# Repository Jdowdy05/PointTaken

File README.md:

# Point Taken — An Optical Tactile Fingertip

A compact optical tactile fingertip built around the **ams OSRAM TMF8829**. A soft silicone surface deforms under contact; the sensor observes the changing distance to its reflective inner layer. Force and contact information must be obtained through calibration.

*Connected electronics and exploded sensor assembly. Cable routing and exploded spacing are schematic.*

*Expected sensing principle. The zone projection and deformation example are illustrative, not calibrated measurements.*

## Repository layout

| Folder | Contents |
| --- | --- |
| [PCBs/](PCBs/) | Native KiCad projects for the five-sensor controller, single-sensor validation rig and fingertip board, plus shared symbols, footprints and 3D reference models. |
| [CAD/Sensor/](CAD/Sensor/) | Corrected sensor housing, one-piece cap retainer, optical parts, compliant-surface geometry, assembled STEP and printable rigid-part STLs. |
| [docs/](docs/) | Material notes, assembly instructions, harness pinout and manufacturer references. |

## Design specifications

| Property | Current design |
| --- | --- |
| Sensing IC | TMF8829 direct time-of-flight sensor; up to **48 ×32 zones** and **940 nm** near-infrared illumination. |
| Sensor enclosure | **24.2 mm wide ×44.5 mm high ×33.8 mm deep**, including the rear locating posts. |
| Fingertip PCB | **10 ×15 mm**, four copper layers, one TMF8829 and four 1.20 mm mounting holes. |
| Main controller | **50 ×50 mm**, six layers, STM32H573ZIT6 and up to five sensor ports; placement complete, **unrouted**. |
| Validation controller | **50 ×40 mm**, six layers, STM32H562RIT6 and one sensor port; routed prototype. |
| Sensor connection | 16-conductor JST NSHD wire harness; SPI primary, optional I3C/I2C lines. |
| Supply architecture | Protected 5 V USB-C controller input; 3.3 V and 1.8 V sensor rails, with an explicit I/O supply. |
| Compliant skin | Nominal **0.90 mm black outer layer +0.30 mm white inner layer**, 1.20 mm total. |
| Target-motion allowance | **6 mm** optical travel allocation; not a measured deformation or force rating. |
| Front retention | **One-piece ring**, three M2 ×6 screws, mechanically captured silicone flange/bead. |
| Rear retention | Two **M2 ×8 screws** for the standalone sensor; side-loaded M2 nuts bear on 4 mm housing shoulders. |

IC capabilities are from the [TMF8829 manufacturer information](https://ams-osram.com/products/sensor-solutions/direct-time-of-flight-sensors-dtof/ams-tmf8829-48x32-multi-zone-time-of-flight-sensor). They do not establish this prototype's effective tactile resolution, frame rate or calibrated force accuracy.

## What the deformable surface should be made from

The current prototype material candidate is **Smooth-On Ecoflex 00-30 platinum-cure silicone**, cast as a bonded two-layer membrane:

- **Outside:** approximately 0.90 mm of black-pigmented silicone to provide the contact surface and block ambient light.
- **Inside:** approximately 0.30 mm of white, titanium-dioxide-filled silicone to provide a diffuse reflective target at 940 nm.

The flexible cap is a cast silicone part. The files in `CAD/Sensor/print/` are the rigid parts intended for 3D printing; compliant-surface meshes describe the casting geometry.

[Ecoflex 00-30 manufacturer instructions](https://www.smooth-on.com/products/ecoflex-00-30/) specify a 1A:1B base mix. Follow the current technical bulletin for preparation and curing. **Pigment/TiO₂ loading and the two-layer bonding process are not yet qualified** for this cap. Black appearance alone does not prove infrared opacity, and white appearance does not establish adequate sensor return. See [Materials](docs/Materials.md) before casting.

## Sensitivity and load targets

These are **design targets, not measured specifications**:

- Detect **0.5 N normal contact**, at least five standard deviations above unloaded repeatability noise over the central 80% of the contact surface.
- Stretch goal: **0.10–0.25 N** detection.
- Produce at least **0.25 mm local target displacement at 0.5–1.0 N** centre load.
- Original mechanical goals: **30 N normal load and 75 N brief overload**. These have not been established for the current cap/housing.

The current state is **a CAD-checked hardware prototype awaiting physical qualification**. CAD clearance checks do not prove sensitivity, tear resistance, layer adhesion, fatigue, creep or overload survival. The single-sensor validation rig and fingertip PCB have routing; the five-sensor controller remains on manufacturing hold. No fabrication or assembly approval is implied by this publication.

## Open and build

1. Open a `.kicad_pro` from [PCBs/](PCBs/) using **KiCad 10** with its standard libraries installed. Project-local library paths are portable.
2. Open [sensor_assembly.step](CAD/Sensor/sensor_assembly.step) in FreeCAD or another STEP-compatible CAD tool. All CAD dimensions are millimetres.
3. Use the **five rigid-part STLs** in [CAD/Sensor/print/](CAD/Sensor/print/), and read the [assembly instructions](docs/Assembly.md). The corrected main housing and one-piece retainer are included.
4. Verify printed nut fits, layer construction and the actual electronics before powered testing. Calibrate the finished silicone article before interpreting deformation as force.

The STEP files provide editable solid geometry; native parametric feature history is not included in this publication. Manufacturer reference documents and component models are identified in [References](docs/References.md).

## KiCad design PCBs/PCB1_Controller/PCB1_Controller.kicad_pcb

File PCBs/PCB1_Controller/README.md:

# PCB1 Controller

Open [PCB1_Controller.kicad_pro](PCB1_Controller.kicad_pro) in KiCad 10.

Five-sensor controller; placement only, zero tracks/vias. Manufacturing hold.

- [Top copper/silkscreen preview](previews/top.svg)
- [Bottom copper/silkscreen preview](previews/bottom.svg)
- [Schematic pages](previews/schematics/)

Keep the shared connector and 3D-model folders alongside the board project. See the [PCB index](../README.md) for library setup and status.

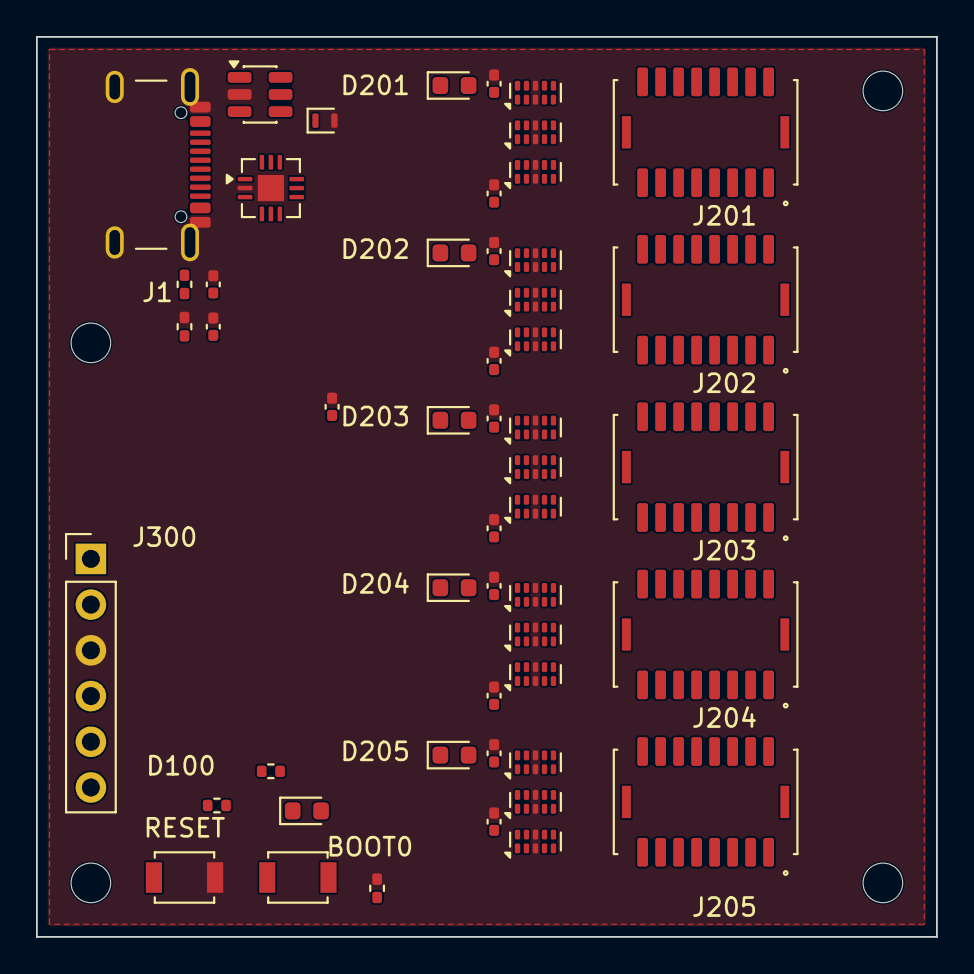
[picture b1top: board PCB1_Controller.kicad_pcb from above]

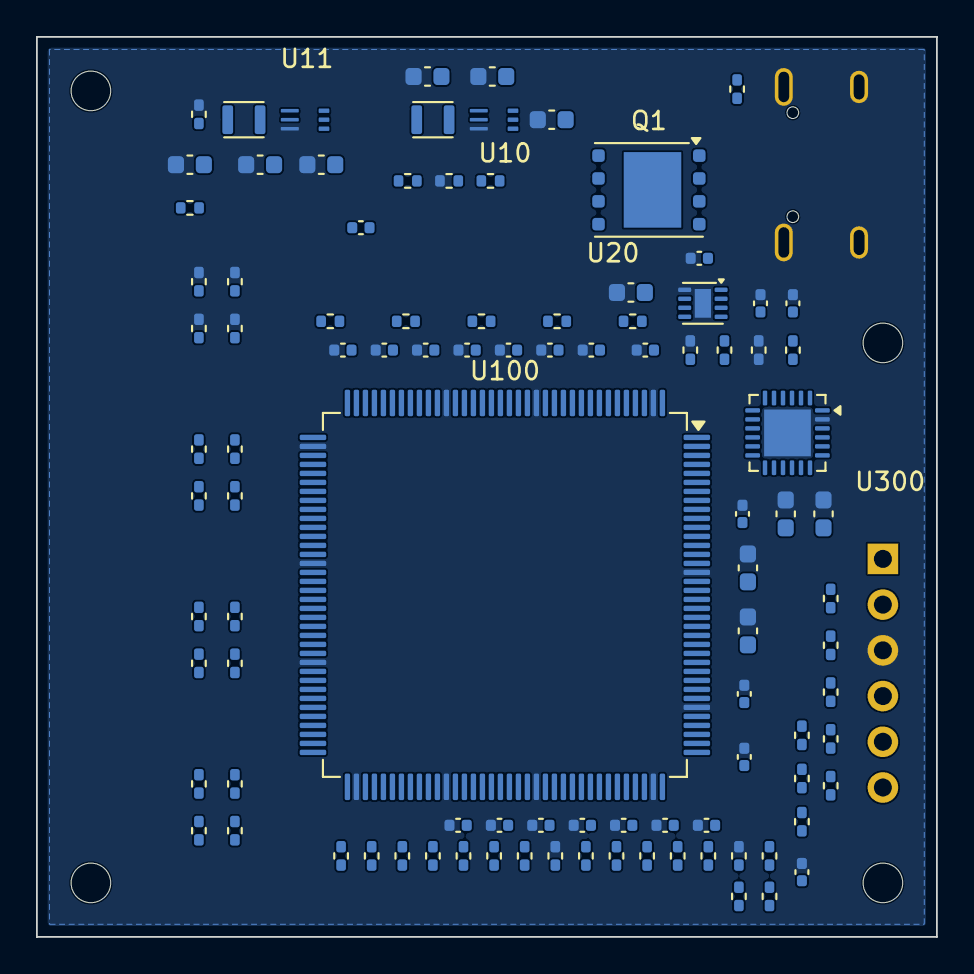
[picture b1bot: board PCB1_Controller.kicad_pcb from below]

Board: 6 copper layers, 50.0 x 50.0 mm, 153 parts (98 on the bottom side), 103 nets, no tracks yet.

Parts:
C1, C2: 330pF; C_0402_1005Metric
C3: 100nF 50V; C_0402_1005Metric
C4: 2.2uF 50V; C_0603_1608Metric
C5, C201, C202, C203, C204, C205, C211, C212, C213, C214, C215, C260, C303: 1uF; C_0402_1005Metric
C6: 3.3nF 50V; C_0402_1005Metric
C10, C20, C330, C340: 4.7uF; C_0603_1608Metric
C11, C12, C21, C22: 10uF; C_0603_1608Metric
C13: 120pF; C_0402_1005Metric
C300, C304, C310, C311, C312, C313, C314, C315, C316, C317, C318, C319, C320, C321, C322, C323, C341, C342: 100nF; C_0402_1005Metric
C301, C302: 2.2uF; C_0603_1608Metric
D1: ESDA25P35-1U1M; ST_QFN-2L_1.6x1.0mm
D100: MCU_STATUS green; LED_0603_1608Metric
D201: TOF1_DATA green; LED_0603_1608Metric
D202: TOF2_DATA green; LED_0603_1608Metric
D203: TOF3_DATA green; LED_0603_1608Metric
D204: TOF4_DATA green; LED_0603_1608Metric
D205: TOF5_DATA green; LED_0603_1608Metric
J1: USB4105-GF-A-120; USB_C_Receptacle_GCT_USB4105-xx-A_16P_TopMnt_Horizontal
J201, J202, J203, J204, J205: BM16B-NSHDZS-TFT; JST_BM16B-NSHDZS-TFT_2x08_P1.00mm_Vertical
J300: TSW-106-07-G-S SWD; PinHeader_1x06_P2.54mm_Vertical
L10, L11: 0.47uH; TDK_TFM201610ALM-R47MTAA_2.0x1.6mm
MH1, MH2, MH3, MH4: M2 2.2mm NPTH; MountingHole_2.2mm_M2
Q1: CSD17577Q5A; TI_CSD17577Q5A_DQJ_VSONP-8_4.9x6.0mm
R1: 80.6k; R_0402_1005Metric
R2: 24k; R_0402_1005Metric
R3, R5, R211, R212, R213, R214, R215, R300, R301: 10k; R_0402_1005Metric
R4, R262, R302, R303, R309: 0R; R_0402_1005Metric
R6: 681R; R_0402_1005Metric
R10: 450k; R_0402_1005Metric
R11, R12, R20, R201, R202, R203, R204, R205, R221, R222, R223, R224, R225, R231, R232, R233, R234, R235, R311, R312: 100k; R_0402_1005Metric
R241, R242, R243, R244, R245, R246, R247, R248, R249, R250: 22R; R_0402_1005Metric
R260, R261: 2.2k; R_0402_1005Metric
R271, R272, R273, R274, R275, R310: 1k; R_0402_1005Metric
R304, R305: 0R DNP; R_0402_1005Metric
R306: 22.1k DNP; R_0402_1005Metric
R307: 47.5k DNP; R_0402_1005Metric
R308: 1k DNP; R_0402_1005Metric
SW100: RESET B3U-1000P; SW_SPST_B3U-1000P
SW101: BOOT0 B3U-1000P; SW_SPST_B3U-1000P
U1: TCPP01-M12; QFN-12-1EP_3x3mm_P0.5mm_EP1.45x1.45mm
U2: USBLC6-2SC6; SOT-23-6
U10: TPS62826DMQ 3.3V; TI_DMQ0006A_VSON-HR-6_1.5x1.5mm
U11: TPS6282618DMQ 1.8V; TI_DMQ0006A_VSON-HR-6_1.5x1.5mm
U20: TPS259531DSGR; DFN-8-1EP_2x2mm_P0.5mm_EP0.9x1.6mm
U100: STM32H573ZIT6; LQFP-144_20x20mm_P0.5mm
U300: CP2102N-A02-GQFN24 DNP; QFN-24-1EP_4x4mm_P0.5mm_EP2.6x2.6mm
U401: ESD204DQA TOF1 SPI; USON-10_2.5x1.0mm_P0.5mm
U402: ESD204DQA TOF1 AUX; USON-10_2.5x1.0mm_P0.5mm
U403: ESD204DQA TOF1 DET; USON-10_2.5x1.0mm_P0.5mm
U404: ESD204DQA TOF2 SPI; USON-10_2.5x1.0mm_P0.5mm
U405: ESD204DQA TOF2 AUX; USON-10_2.5x1.0mm_P0.5mm
U406: ESD204DQA TOF2 DET; USON-10_2.5x1.0mm_P0.5mm
U407: ESD204DQA TOF3 SPI; USON-10_2.5x1.0mm_P0.5mm
U408: ESD204DQA TOF3 AUX; USON-10_2.5x1.0mm_P0.5mm
U409: ESD204DQA TOF3 DET; USON-10_2.5x1.0mm_P0.5mm
U410: ESD204DQA TOF4 SPI; USON-10_2.5x1.0mm_P0.5mm
U411: ESD204DQA TOF4 AUX; USON-10_2.5x1.0mm_P0.5mm
U412: ESD204DQA TOF4 DET; USON-10_2.5x1.0mm_P0.5mm
U413: ESD204DQA TOF5 SPI; USON-10_2.5x1.0mm_P0.5mm
U414: ESD204DQA TOF5 AUX; USON-10_2.5x1.0mm_P0.5mm
U415: ESD204DQA TOF5 DET; USON-10_2.5x1.0mm_P0.5mm

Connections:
BOOT0: R301.1, SW101.1, U100.138
CC1_CONN: C1.1, J1.A5, U1.7
CC2_CONN: C2.1, J1.B5, U1.9
CP2102_DM: R305.2, U300.4
CP2102_DP: R304.2, U300.3
CP2102_RST_N: R308.2, U300.9
CP2102_VBUS_SENSE: R306.2, R307.1, U300.8
EFUSE_DVDT: C6.1, U20.1
EFUSE_FLT_N: R5.2, U20.6, U100.125
EFUSE_ILM: R6.1, U20.7
FB_3V3: C13.2, R10.2, R11.1, U10.3
GND: C1.2, C2.2, C3.2, C4.2, C5.2, C6.2, C10.2, C11.2, C12.2, C20.2, C21.2, C22.2, C201.2, C202.2, C203.2, C204.2, C205.2, C211.2, C212.2, C213.2, C214.2, C215.2, C260.2, C300.2, C301.2, C302.2, C303.2, C304.2, C310.2, C311.2, C312.2, C313.2, C314.2, C315.2, C316.2, C317.2, C318.2, C319.2, C320.2, C321.2, C322.2, C323.2, C330.2, C340.2, C341.2, C342.2, D1.2, J1.A1, J1.A12, J1.B1, J1.B12, J1.SH, J300.3, R2.2, R4.1, R4.2, R6.2, R11.2, R201.2, R202.2, R203.2, R204.2, R205.2, R301.2, R307.2, R312.2, SW100.2, U1.2, U1.13, U2.2, U10.4, U11.4, U20.8, U20.9, U100.16, U100.31, U100.38, U100.51, U100.61, U100.71, U100.83, U100.94, U100.107, U100.120, U100.130, U100.143, U300.2, U300.25, U401.3, U401.8, U402.3, U402.8, U403.3, U403.8, U404.3, U404.8, U405.3, U405.8, U406.3, U406.8, U407.3, U407.8, U408.3, U408.8, U409.3, U409.8, U410.3, U410.8, U411.3, U411.8, U412.3, U412.8, U413.3, U413.8, U414.3, U414.8, U415.3, U415.8
I3C1_SCL_SHARED: R260.2, U100.136, U402.1, U405.1, U408.1, U411.1, U414.1
I3C1_SDA_SHARED: R261.2, U100.137, U402.2, U405.2, U408.2, U411.2, U414.2
MCU_STATUS_LED_A: D100.2, R310.2
MCU_STATUS_LED_N: D100.1, U100.124
MCU_UART_RX: U100.78, U300.21
MCU_UART_TX: U100.77, U300.20
NRST_N: C300.1, J300.5, R300.2, SW100.1, U100.25
P1V8_TOF: C21.1, C22.1, C211.1, C212.1, C213.1, C214.1, C215.1, L11.2, U11.3
P3V3: C11.1, C12.1, C13.1, C201.1, C202.1, C203.1, C204.1, C205.1, C310.1, C311.1, C312.1, C313.1, C314.1, C315.1, C316.1, C317.1, C318.1, C319.1, C320.1, C321.1, C322.1, C323.1, C330.1, C340.1, C341.1, J300.1, L10.2, R3.1, R5.1, R10.1, R12.1, R20.1, R262.1, R271.1, R272.1, R273.1, R274.1, R275.1, R300.1, R308.1, R309.1, R310.1, SW101.2, U1.12, U100.6, U100.17, U100.30, U100.39, U100.52, U100.62, U100.72, U100.84, U100.95, U100.106, U100.108, U100.121, U100.131, U100.144, U300.5, U300.6, U300.7
PGOOD_1V8: R20.2, U11.2
PGOOD_3V3: R12.2, U10.2
SPI1_MISO: U100.42, U401.4
SPI1_MOSI: R242.2, U401.2
SPI1_MOSI_MCU: R242.1, U100.43
SPI1_SCK: R241.2, U401.1
SPI1_SCK_MCU: R241.1, U100.41
SPI2_MISO: U100.28, U404.4
SPI2_MOSI: R244.2, U404.2
SPI2_MOSI_MCU: R244.1, U100.29
SPI2_SCK: R243.2, U404.1
SPI2_SCK_MCU: R243.1, U100.69
SPI3_MISO: U100.112, U407.4
SPI3_MOSI: R246.2, U407.2
SPI3_MOSI_MCU: R246.1, U100.113
SPI3_SCK: R245.2, U407.1
SPI3_SCK_MCU: R245.1, U100.111
SPI4_MISO: U100.66, U410.4
SPI4_MOSI: R248.2, U410.2
SPI4_MOSI_MCU: R248.1, U100.67
SPI4_SCK: R247.2, U410.1
SPI4_SCK_MCU: R247.1, U100.65
SPI5_MISO: U100.20, U413.4
SPI5_MOSI: R250.2, U413.2
SPI5_MOSI_MCU: R250.1, U100.21
SPI5_SCK: R249.2, U413.1
SPI5_SCK_MCU: R249.1, U100.19
STM_USB_DM: R303.2, U100.103
STM_USB_DP: R302.2, U100.104
SWCLK: J300.4, U100.109
SWDIO: J300.2, U100.105
SWO: J300.6, U100.133
SW_1V8: L11.1, U11.5
SW_3V3: L10.1, U10.5
TCPP_DB_N: U1.10, U100.101
TCPP_FLT_N: R3.2, U1.11, U100.98
TOF1_CS_N: R231.2, U100.40, U401.5
TOF1_DET: R221.2, U100.26, U403.1
TOF1_EN: R201.1, U100.79, U402.4
TOF1_INT: R211.2, U100.80, U402.5
TOF1_LED_A: D201.2, R271.2
TOF1_LED_N: D201.1, U100.89
TOF2_CS_N: R232.2, U100.37, U404.5
TOF2_DET: R222.2, U100.27, U406.1
TOF2_EN: R202.1, U100.81, U405.4
TOF2_INT: R212.2, U100.82, U405.5
TOF2_LED_A: D202.2, R272.2
TOF2_LED_N: D202.1, U100.90
TOF3_CS_N: R233.2, U100.116, U407.5
TOF3_DET: R223.2, U100.44, U409.1
TOF3_EN: R203.1, U100.58, U408.4
TOF3_INT: R213.2, U100.59, U408.5
TOF3_LED_A: D203.2, R273.2
TOF3_LED_N: D203.1, U100.91
TOF4_CS_N: R234.2, U100.64, U410.5
TOF4_DET: R224.2, U100.45, U412.1
TOF4_EN: R204.1, U100.60, U411.4
TOF4_INT: R214.2, U100.63, U411.5
TOF4_LED_A: D204.2, R274.2
TOF4_LED_N: D204.1, U100.92
TOF5_CS_N: R235.2, U100.18, U413.5
TOF5_DET: R225.2, U100.34, U415.1
TOF5_EN: R205.1, U100.87, U414.4
TOF5_INT: R215.2, U100.88, U414.5
TOF5_LED_A: D205.2, R275.2
TOF5_LED_N: D205.1, U100.93
TOF_VIO: C260.1, R211.1, R212.1, R213.1, R214.1, R215.1, R221.1, R222.1, R223.1, R224.1, R225.1, R231.1, R232.1, R233.1, R234.1, R235.1, R260.1, R261.1, R262.2
UCPD_CC1: U1.3, U100.74
UCPD_CC2: U1.1, U100.75
USB_DM_CONN: J1.A7, J1.B7, U2.3
USB_DM_PROT: R303.1, R305.1, U2.4
USB_DP_CONN: J1.A6, J1.B6, U2.1
USB_DP_PROT: R302.1, R304.1, U2.6
VBUS_CTRL: R1.2, R2.1, U1.6
VBUS_FUSED: C5.1, C10.1, C20.1, R311.1, U10.1, U10.6, U11.1, U11.6, U20.5
VBUS_GATE: Q1.5, U1.5
VBUS_IN: D1.1, J1.A4, J1.A9, J1.B4, J1.B9, Q1.1, Q1.2, Q1.3, Q1.4, R1.1, U1.8, U2.5
VBUS_SENSE_ADC: C342.1, R311.2, R312.1, U100.35
VBUS_SYS: C3.1, C4.1, Q1.6, Q1.7, Q1.8, R306.1, U1.4, U20.2, U20.3, U20.4
VCAP1: C301.1, U100.70
VCAP2: C302.1, U100.142
VDDA_3V3: C303.1, C304.1, R309.2, U100.32, U100.33

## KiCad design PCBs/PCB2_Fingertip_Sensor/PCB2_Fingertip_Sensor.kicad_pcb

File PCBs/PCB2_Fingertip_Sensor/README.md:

# PCB2 Fingertip Sensor

Open [PCB2_Fingertip_Sensor.kicad_pro](PCB2_Fingertip_Sensor.kicad_pro) in KiCad 10.

Routed prototype. Native source is included; physical bring-up and manufacturing review remain necessary.

- [Top copper/silkscreen preview](previews/top.svg)
- [Bottom copper/silkscreen preview](previews/bottom.svg)
- [Schematic pages](previews/schematics/)

Keep the shared connector and 3D-model folders alongside the board project. See the [PCB index](../README.md) for library setup and status.

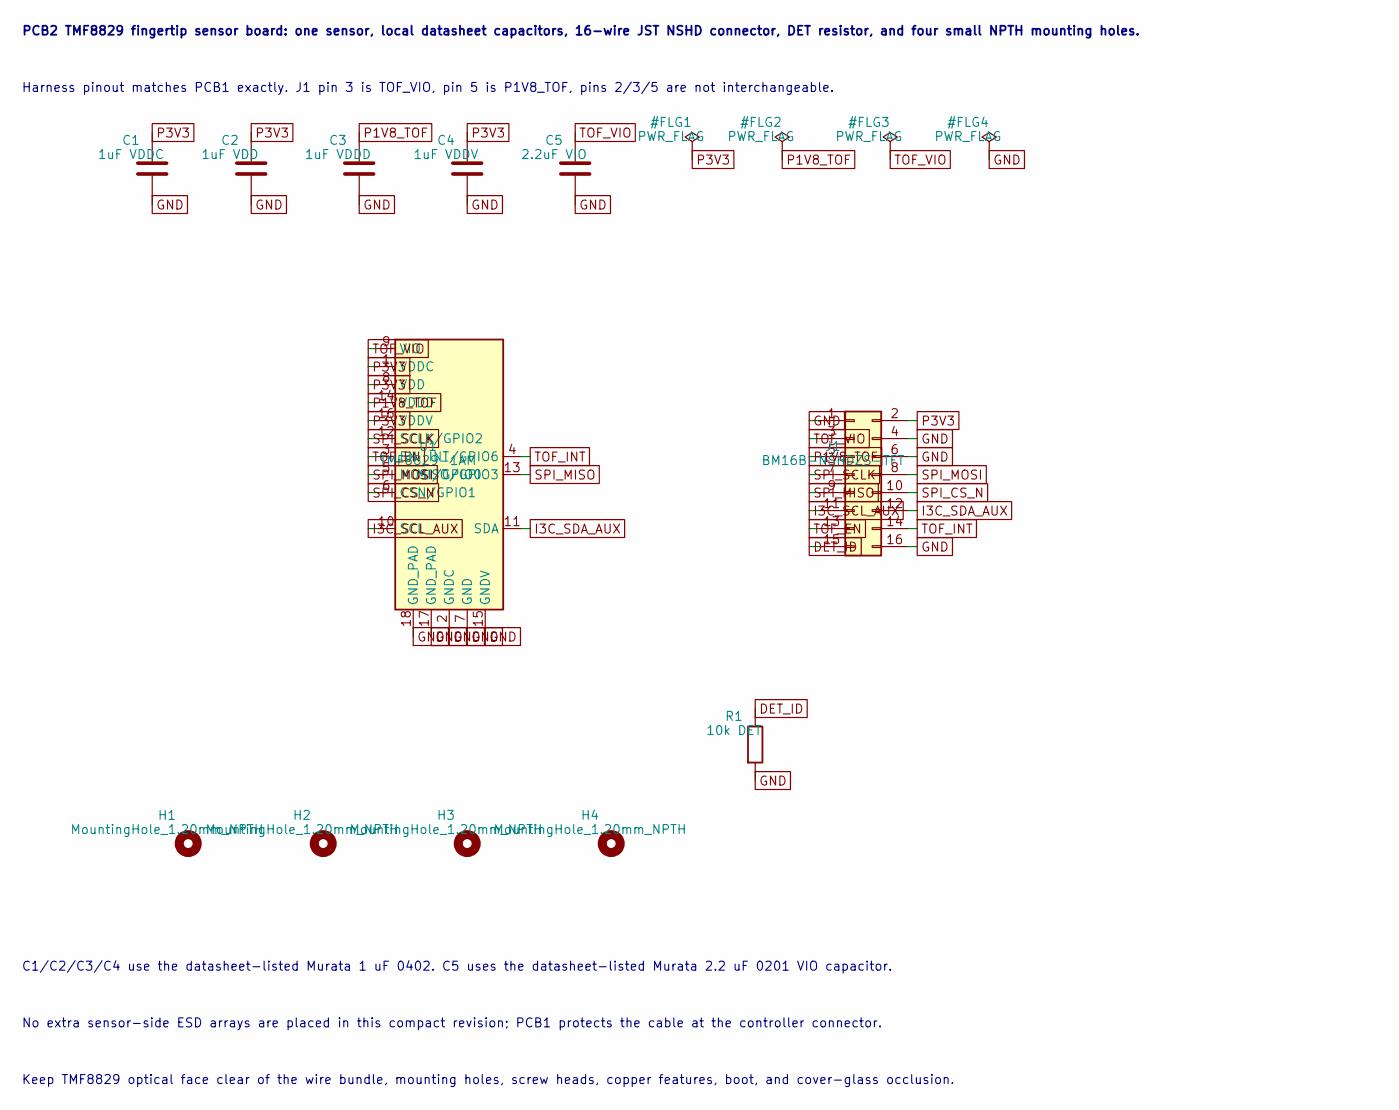
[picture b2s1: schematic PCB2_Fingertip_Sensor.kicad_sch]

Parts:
C1: 1uF VDDC; C_0402_1005Metric; MPN GRM155R70J105KA12
C2: 1uF VDD; C_0402_1005Metric; MPN GRM155R70J105KA12
C3: 1uF VDDD; C_0402_1005Metric; MPN GRM155R70J105KA12
C4: 1uF VDDV; C_0402_1005Metric; MPN GRM155R70J105KA12
C5: 2.2uF VIO; C_0201_0603Metric; MPN GRM033R60J225ME47
H1, H2, H3, H4: MountingHole_1.20mm_NPTH
J1: BM16B-NSHDZS-TFT; JST_BM16B-NSHDZS-TFT_2x08_P1.00mm_Vertical; MPN BM16B-NSHDZS-TFT; DigiKey_PN 455-BM16B-NSHDZS-TFTCT-ND
R1: 10k DET; R_0402_1005Metric; MPN RC0402FR-0710KL
U1: TMF8829-1AM; ams_OSRAM_TMF8829_OLGA-18_5.7x2.9mm; MPN TMF8829-1AM

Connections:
DET_ID: J1.15, R1.1
GND: C1.2, C2.2, C3.2, C4.2, C5.2, J1.1, J1.4, J1.6, J1.16, R1.2, U1.2 (GNDC), U1.7 (GND), U1.15 (GNDV), U1.17 (GND_PAD), U1.18 (GND_PAD)
I3C_SCL_AUX: J1.11, U1.10 (SCL)
I3C_SDA_AUX: J1.12, U1.11 (SDA)
P1V8_TOF: C3.1, J1.5, U1.14 (VDDD)
P3V3: C1.1, C2.1, C4.1, J1.2, U1.1 (VDDC), U1.8 (VDD), U1.16 (VDDV)
SPI_CS_N: J1.10, U1.6 (CSN/GPIO1)
SPI_MISO: J1.9, U1.13 (MISO/GPIO3)
SPI_MOSI: J1.8, U1.5 (MOSI/GPIO0)
SPI_SCLK: J1.7, U1.12 (SCLK/GPIO2)
TOF_EN: J1.13, U1.3 (EN)
TOF_INT: J1.14, U1.4 (INT/GPIO6)
TOF_VIO: C5.1, J1.3, U1.9 (VIO)

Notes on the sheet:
PCB2 TMF8829 fingertip sensor board: one sensor, local datasheet capacitors, 16-wire JST NSHD connector, DET resistor, and four small NPTH mounting holes.
Harness pinout matches PCB1 exactly. J1 pin 3 is TOF_VIO, pin 5 is P1V8_TOF, pins 2/3/5 are not interchangeable.
C1/C2/C3/C4 use the datasheet-listed Murata 1 uF 0402. C5 uses the datasheet-listed Murata 2.2 uF 0201 VIO capacitor.
No extra sensor-side ESD arrays are placed in this compact revision; PCB1 protects the cable at the controller connector.
Keep TMF8829 optical face clear of the wire bundle, mounting holes, screw heads, copper features, boot, and cover-glass occlusion.

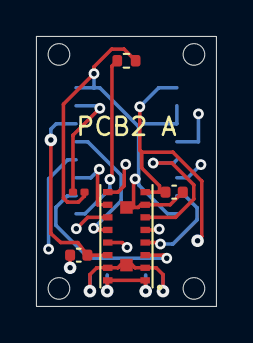
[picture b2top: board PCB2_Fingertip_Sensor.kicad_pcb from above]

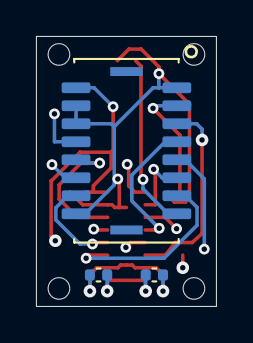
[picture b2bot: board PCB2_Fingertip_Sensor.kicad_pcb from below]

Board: 4 copper layers, 10.0 x 15.0 mm, 12 parts (3 on the bottom side), 13 nets.

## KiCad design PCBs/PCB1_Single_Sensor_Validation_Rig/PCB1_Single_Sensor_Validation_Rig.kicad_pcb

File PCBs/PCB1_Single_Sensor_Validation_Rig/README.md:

# PCB1 Single Sensor Validation Rig

Open [PCB1_Single_Sensor_Validation_Rig.kicad_pro](PCB1_Single_Sensor_Validation_Rig.kicad_pro) in KiCad 10.

Routed prototype. Native source is included; physical bring-up and manufacturing review remain necessary.

- [Top copper/silkscreen preview](previews/top.svg)
- [Bottom copper/silkscreen preview](previews/bottom.svg)
- [Schematic pages](previews/schematics/)

Keep the shared connector and 3D-model folders alongside the board project. See the [PCB index](../README.md) for library setup and status.

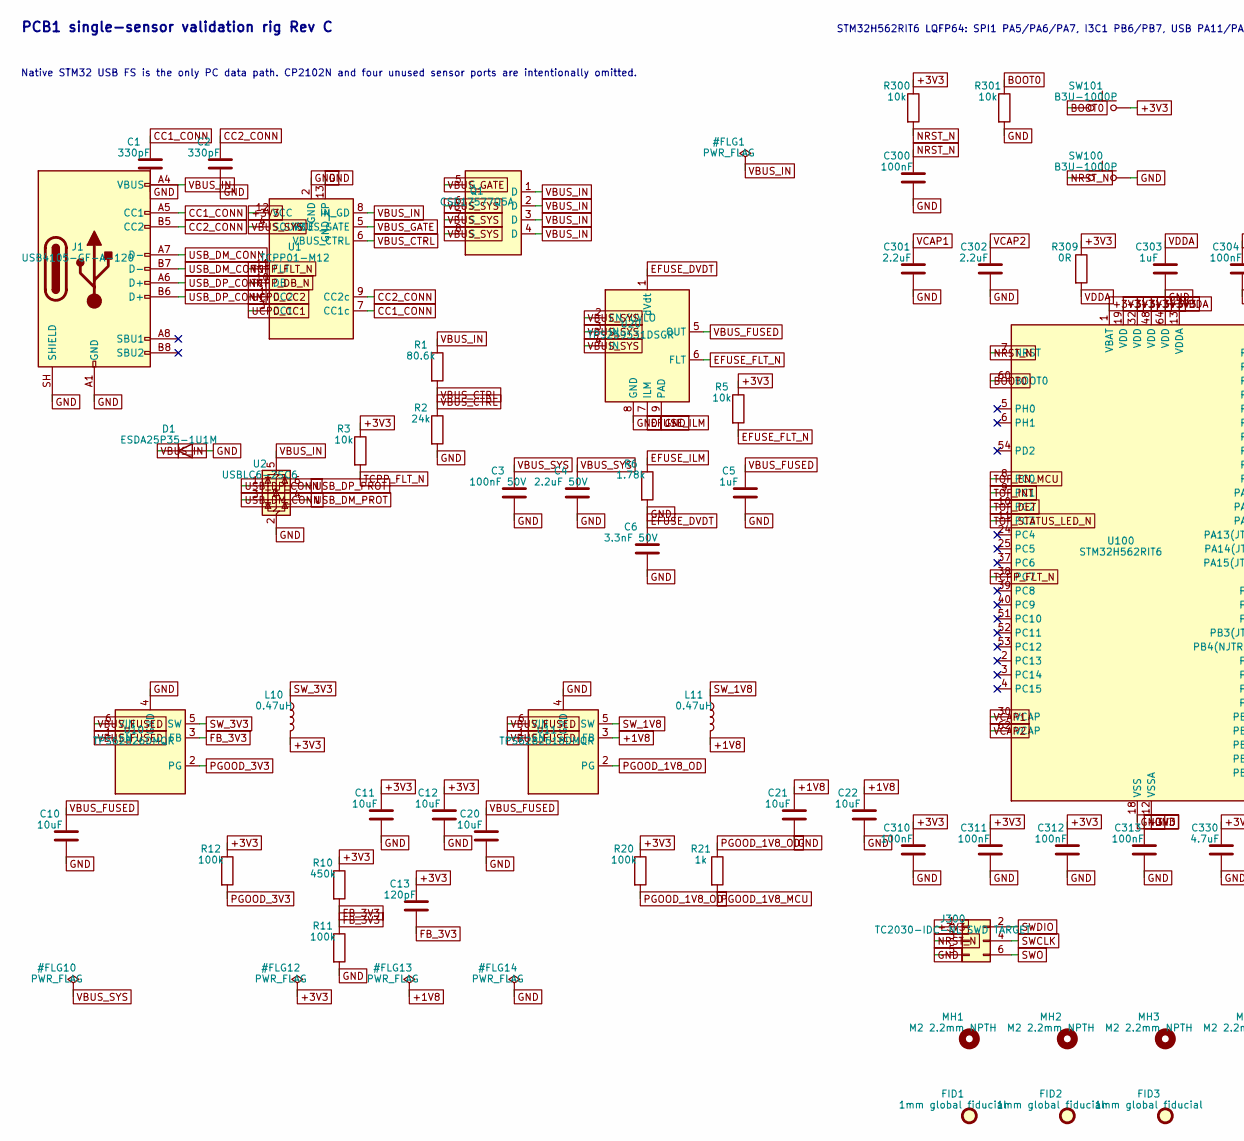
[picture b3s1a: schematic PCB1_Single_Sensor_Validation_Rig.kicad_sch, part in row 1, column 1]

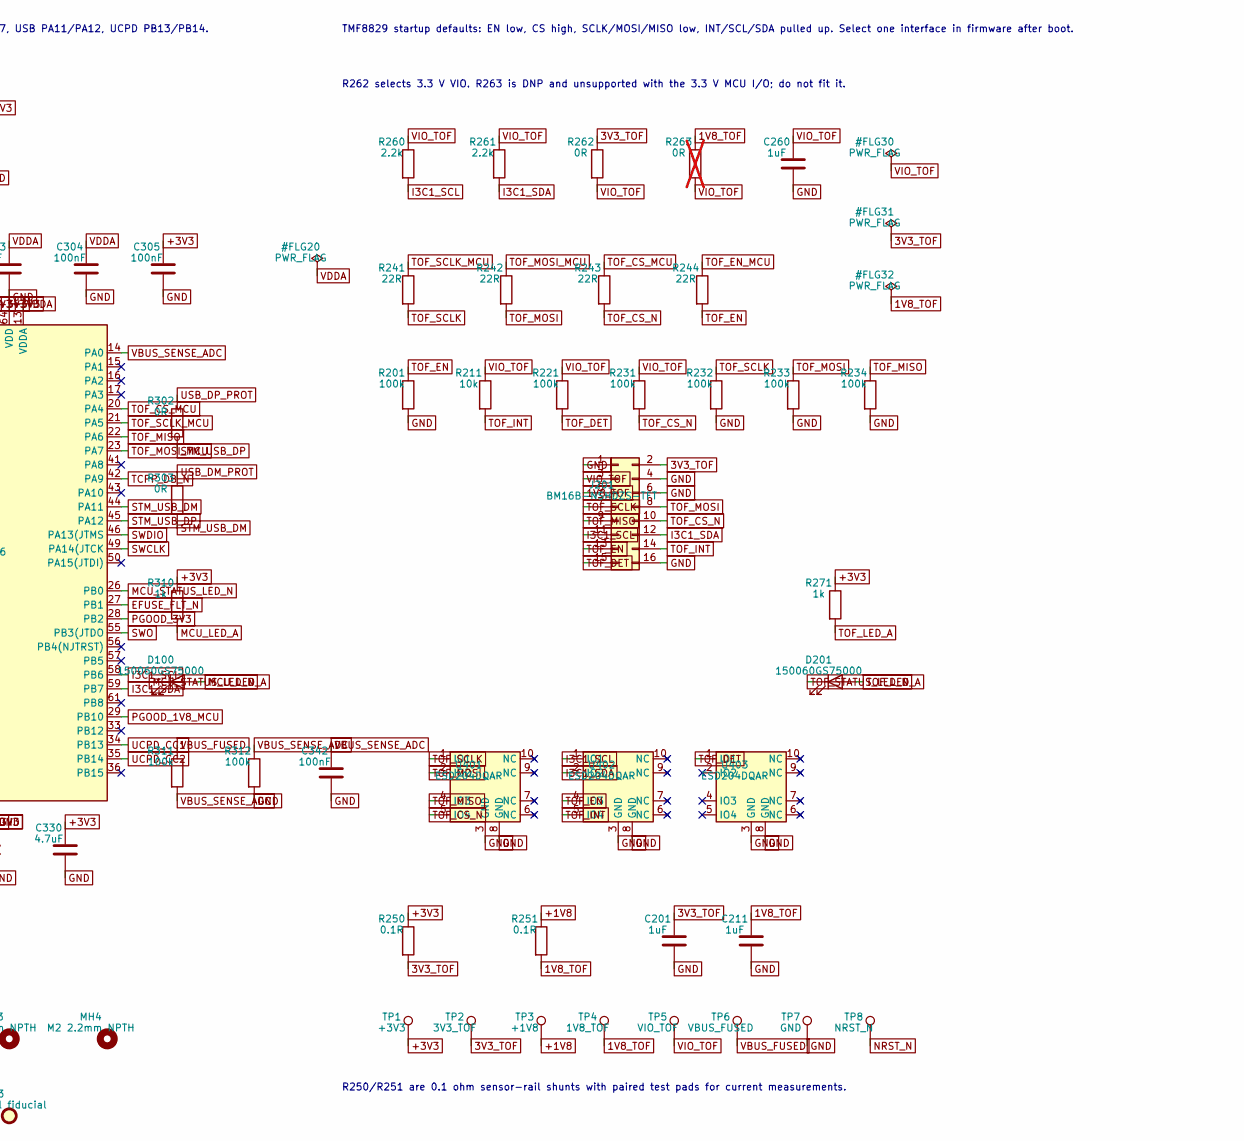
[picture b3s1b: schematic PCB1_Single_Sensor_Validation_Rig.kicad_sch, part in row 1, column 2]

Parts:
C1, C2: 330pF; C_0402_1005Metric; MPN GRM1555C1H331GA01D
C3: 100nF 50V; C_0402_1005Metric; MPN GRM155R71H104KE14D
C4: 2.2uF 50V; C_0603_1608Metric; MPN GRM188R61H225KE11D
C5, C201, C211, C260, C303: 1uF; C_0402_1005Metric; MPN GRM155R61A105KE15D
C6: 3.3nF 50V; C_0402_1005Metric; MPN GRM155R71H332KA01D
C10, C11, C12, C20, C21, C22: 10uF; C_0603_1608Metric; MPN GRM188Z71A106MA73D
C13: 120pF; C_0402_1005Metric; MPN GRM1555C1H121JA01D
C300, C304, C305, C310, C311, C312, C313, C342: 100nF; C_0402_1005Metric; MPN GRM155R71C104KA88D
C301, C302: 2.2uF; C_0603_1608Metric; MPN GRM188R61H225KE11D
C330: 4.7uF; C_0603_1608Metric; MPN GRM188R60J475KE19D
D1: ESDA25P35-1U1M; ST_QFN-2L_1.6x1.0mm; MPN ESDA25P35-1U1M
D100, D201: 150060GS75000; LED_0603_1608Metric; MPN 150060GS75000
FID1, FID2, FID3: 1mm global fiducial; Fiducial_1mm_Mask2mm
J1: USB4105-GF-A-120; USB_C_Receptacle_GCT_USB4105-xx-A_16P_TopMnt_Horizontal; MPN USB4105-GF-A-120
J201: BM16B-NSHDZS-TFT; JST_BM16B-NSHDZS-TFT_2x08_P1.00mm_Vertical; MPN BM16B-NSHDZS-TFT
J300: TC2030-IDC-NL SWD TARGET; Tag-Connect_TC2030-IDC-NL_2x03_P1.27mm_Vertical; MPN TC2030-IDC-NL
L10, L11: 0.47uH; TDK_TFM201610ALM-R47MTAA_2.0x1.6mm; MPN TFM201610ALM-R47MTAA
MH1, MH2, MH3, MH4: M2 2.2mm NPTH; MountingHole_2.2mm_M2
Q1: CSD17577Q5A; TI_CSD17577Q5A_DQJ_VSONP-8_4.9x6.0mm; MPN CSD17577Q5A
R1: 80.6k; R_0402_1005Metric; MPN RC0402FR-0780K6L
R2: 24k; R_0402_1005Metric; MPN RC0402FR-0724KL
R3, R5, R211, R300, R301: 10k; R_0402_1005Metric; MPN RC0402FR-0710KL
R6: 1.78k; R_0402_1005Metric; MPN RC0402FR-071K78L
R10: 450k; R_0402_1005Metric; MPN FRC0402F4503TS
R11, R12, R20, R201, R221, R231, R232, R233, R234, R311, R312: 100k; R_0402_1005Metric; MPN RC0402FR-07100KL
R21, R271, R310: 1k; R_0402_1005Metric; MPN RC0402FR-071KL
R241, R242, R243, R244: 22R; R_0402_1005Metric; MPN RC0402FR-0722RL
R250, R251: 0.1R; R_0402_1005Metric; MPN RL0402FR-070R1L
R260, R261: 2.2k; R_0402_1005Metric; MPN RC0402FR-072K2L
R262, R302, R303, R309: 0R; R_0402_1005Metric; MPN RC0402JR-070RL
R263: 0R; R_0402_1005Metric; MPN RC0402JR-070RL; not fitted
SW100, SW101: B3U-1000P; SW_SPST_B3U-1000P; MPN B3U-1000P
TP1: +3V3; TestPoint_Pad_D1.0mm
TP2: 3V3_TOF; TestPoint_Pad_D1.0mm
TP3: +1V8; TestPoint_Pad_D1.0mm
TP4: 1V8_TOF; TestPoint_Pad_D1.0mm
TP5: VIO_TOF; TestPoint_Pad_D1.0mm
TP6: VBUS_FUSED; TestPoint_Pad_D1.0mm
TP7: GND; TestPoint_Pad_D1.0mm
TP8: NRST_N; TestPoint_Pad_D1.0mm
U1: TCPP01-M12; QFN-12-1EP_3x3mm_P0.5mm_EP1.45x1.45mm; MPN TCPP01-M12
U2: USBLC6-2SC6; SOT-23-6; MPN USBLC6-2SC6
U10: TPS62826DMQR; TI_DMQ0006A_VSON-HR-6_1.5x1.5mm; MPN TPS62826DMQR
U11: TPS6282618DMQR; TI_DMQ0006A_VSON-HR-6_1.5x1.5mm; MPN TPS6282618DMQR
U20: TPS259531DSGR; DFN-8-1EP_2x2mm_P0.5mm_EP0.9x1.6mm; MPN TPS259531DSGR
U100: STM32H562RIT6; LQFP-64_10x10mm_P0.5mm; MPN STM32H562RIT6
U401, U402, U403: ESD204DQAR; USON-10_2.5x1.0mm_P0.5mm; MPN ESD204DQAR

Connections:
1V8_TOF: C211.1, J201.5, R251.2, R263.1, TP4.1
3V3_TOF: C201.1, J201.2, R250.2, R262.1, TP2.1
+1V8: C21.1, C22.1, L11.2, R251.1, TP3.1, U11.3 (FB)
+3V3: C11.1, C12.1, C13.1, C305.1, C310.1, C311.1, C312.1, C313.1, C330.1, J300.1, L10.2, R3.1, R5.1, R10.1, R12.1, R20.1, R250.1, R271.1, R300.1, R309.1, R310.1, SW101.2, TP1.1, U1.12 (VCC), U100.1 (VBAT), U100.19 (VDD), U100.32 (VDD), U100.48 (VDD), U100.64 (VDD)
BOOT0: R301.1, SW101.1, U100.60 (BOOT0)
CC1_CONN: C1.1, J1.A5 (CC1), U1.7 (CC1c)
CC2_CONN: C2.1, J1.B5 (CC2), U1.9 (CC2c)
EFUSE_DVDT: C6.1, U20.1 (dVdt)
EFUSE_FLT_N: R5.2, U20.6 (FLT), U100.27 (PB1)
EFUSE_ILM: R6.1, U20.7 (ILM)
FB_3V3: C13.2, R10.2, R11.1, U10.3 (FB)
GND: C1.2, C2.2, C3.2, C4.2, C5.2, C6.2, C10.2, C11.2, C12.2, C20.2, C21.2, C22.2, C201.2, C211.2, C260.2, C300.2, C301.2, C302.2, C303.2, C304.2, C305.2, C310.2, C311.2, C312.2, C313.2, C330.2, C342.2, D1.2 (A), J1.A1 (GND), J1.A12 (GND), J1.B1 (GND), J1.B12 (GND), J1.SH (SHIELD), J201.1, J201.4, J201.6, J201.16, J300.5, R2.2, R6.2, R11.2, R201.2, R232.2, R233.2, R234.2, R301.2, R312.2, SW100.2, TP7.1, U1.2 (GND), U1.13 (GND_EP), U2.2 (GND), U10.4 (GND), U11.4 (GND), U20.8 (GND), U20.9 (PAD), U100.12 (VSSA), U100.18 (VSS), U100.31 (VSS), U100.47 (VSS), U100.63 (VSS), U401.3 (GND), U401.8 (GND), U402.3 (GND), U402.8 (GND), U403.3 (GND), U403.8 (GND)
I3C1_SCL: J201.11, R260.2, U100.58 (PB6), U402.1 (IO1)
I3C1_SDA: J201.12, R261.2, U100.59 (PB7), U402.2 (IO2)
MCU_LED_A: D100.2 (A), R310.2
MCU_STATUS_LED_N: D100.1 (K), U100.26 (PB0)
NRST_N: C300.1, J300.3, R300.2, SW100.1, TP8.1, U100.7 (NRST)
PGOOD_1V8_MCU: R21.2, U100.29 (PB10)
PGOOD_1V8_OD: R20.2, R21.1, U11.2 (PG)
PGOOD_3V3: R12.2, U10.2 (PG), U100.28 (PB2)
STM_USB_DM: R303.2, U100.44 (PA11)
STM_USB_DP: R302.2, U100.45 (PA12)
SWCLK: J300.4, U100.49 (PA14(JTCK)
SWDIO: J300.2, U100.46 (PA13(JTMS)
SWO: J300.6, U100.55 (PB3(JTDO)
SW_1V8: L11.1, U11.5 (SW)
SW_3V3: L10.1, U10.5 (SW)
TCPP_DB_N: U1.10 (DB), U100.42 (PA9)
TCPP_FLT_N: R3.2, U1.11 (FLT), U100.38 (PC7)
TOF_CS_MCU: R243.1, U100.20 (PA4)
TOF_CS_N: J201.10, R231.2, R243.2, U401.5 (IO4)
TOF_DET: J201.15, R221.2, U100.10 (PC2), U403.1 (IO1)
TOF_EN: J201.13, R201.1, R244.2, U402.4 (IO3)
TOF_EN_MCU: R244.1, U100.8 (PC0)
TOF_INT: J201.14, R211.2, U100.9 (PC1), U402.5 (IO4)
TOF_LED_A: D201.2 (A), R271.2
TOF_MISO: J201.9, R234.1, U100.22 (PA6), U401.4 (IO3)
TOF_MOSI: J201.8, R233.1, R242.2, U401.2 (IO2)
TOF_MOSI_MCU: R242.1, U100.23 (PA7)
TOF_SCLK: J201.7, R232.1, R241.2, U401.1 (IO1)
TOF_SCLK_MCU: R241.1, U100.21 (PA5)
TOF_STATUS_LED_N: D201.1 (K), U100.11 (PC3)
UCPD_CC1: U1.3 (CC1), U100.34 (PB13)
UCPD_CC2: U1.1 (CC2), U100.35 (PB14)
USB_DM_CONN: J1.A7 (D-), J1.B7 (D-), U2.3 (I/O2)
USB_DM_PROT: R303.1, U2.4 (I/O2)
USB_DP_CONN: J1.A6 (D+), J1.B6 (D+), U2.1 (I/O1)
USB_DP_PROT: R302.1, U2.6 (I/O1)
VBUS_CTRL: R1.2, R2.1, U1.6 (VBUS_CTRL)
VBUS_FUSED: C5.1, C10.1, C20.1, R311.1, TP6.1, U10.1 (EN), U10.6 (VIN), U11.1 (EN), U11.6 (VIN), U20.5 (OUT)
VBUS_GATE: Q1.5 (G), U1.5 (VBUS_GATE)
VBUS_IN: D1.1 (K), J1.A4 (VBUS), J1.A9 (VBUS), J1.B4 (VBUS), J1.B9 (VBUS), Q1.1 (D), Q1.2 (D), Q1.3 (D), Q1.4 (D), R1.1, U1.8 (IN_GD), U2.5 (VBUS)
VBUS_SENSE_ADC: C342.1, R311.2, R312.1, U100.14 (PA0)
VBUS_SYS: C3.1, C4.1, Q1.6 (S), Q1.7 (S), Q1.8 (S), U1.4 (SOURCE), U20.2 (EN/UVLO), U20.3 (IN), U20.4 (IN)
VCAP1: C301.1, U100.30 (VCAP)
VCAP2: C302.1, U100.62 (VCAP)
VDDA: C303.1, C304.1, R309.2, U100.13 (VDDA)
VIO_TOF: C260.1, J201.3, R211.1, R221.1, R231.1, R260.1, R261.1, R262.2, R263.2, TP5.1

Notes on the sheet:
PCB1 single-sensor validation rig Rev C
Native STM32 USB FS is the only PC data path. CP2102N and four unused sensor ports are intentionally omitted.
STM32H562RIT6 LQFP64: SPI1 PA5/PA6/PA7, I3C1 PB6/PB7, USB PA11/PA12, UCPD PB13/PB14.
TMF8829 startup defaults: EN low, CS high, SCLK/MOSI/MISO low, INT/SCL/SDA pulled up. Select one interface in firmware after boot.
R262 selects 3.3 V VIO. R263 is DNP and unsupported with the 3.3 V MCU I/O; do not fit it.
R250/R251 are 0.1 ohm sensor-rail shunts with paired test pads for current measurements.

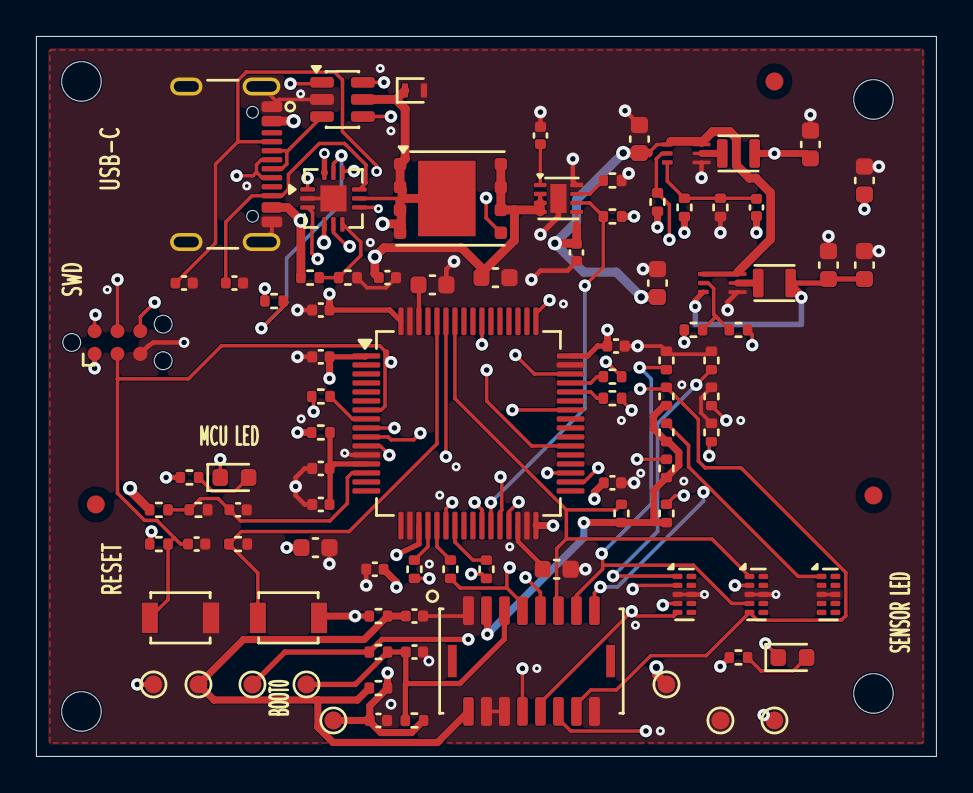
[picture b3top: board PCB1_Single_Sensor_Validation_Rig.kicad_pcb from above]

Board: 6 copper layers, 50.0 x 40.0 mm, 99 parts (0 on the bottom side), 58 nets.

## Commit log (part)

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2026-06-11 Add TMF8829 PCB documentation vault
